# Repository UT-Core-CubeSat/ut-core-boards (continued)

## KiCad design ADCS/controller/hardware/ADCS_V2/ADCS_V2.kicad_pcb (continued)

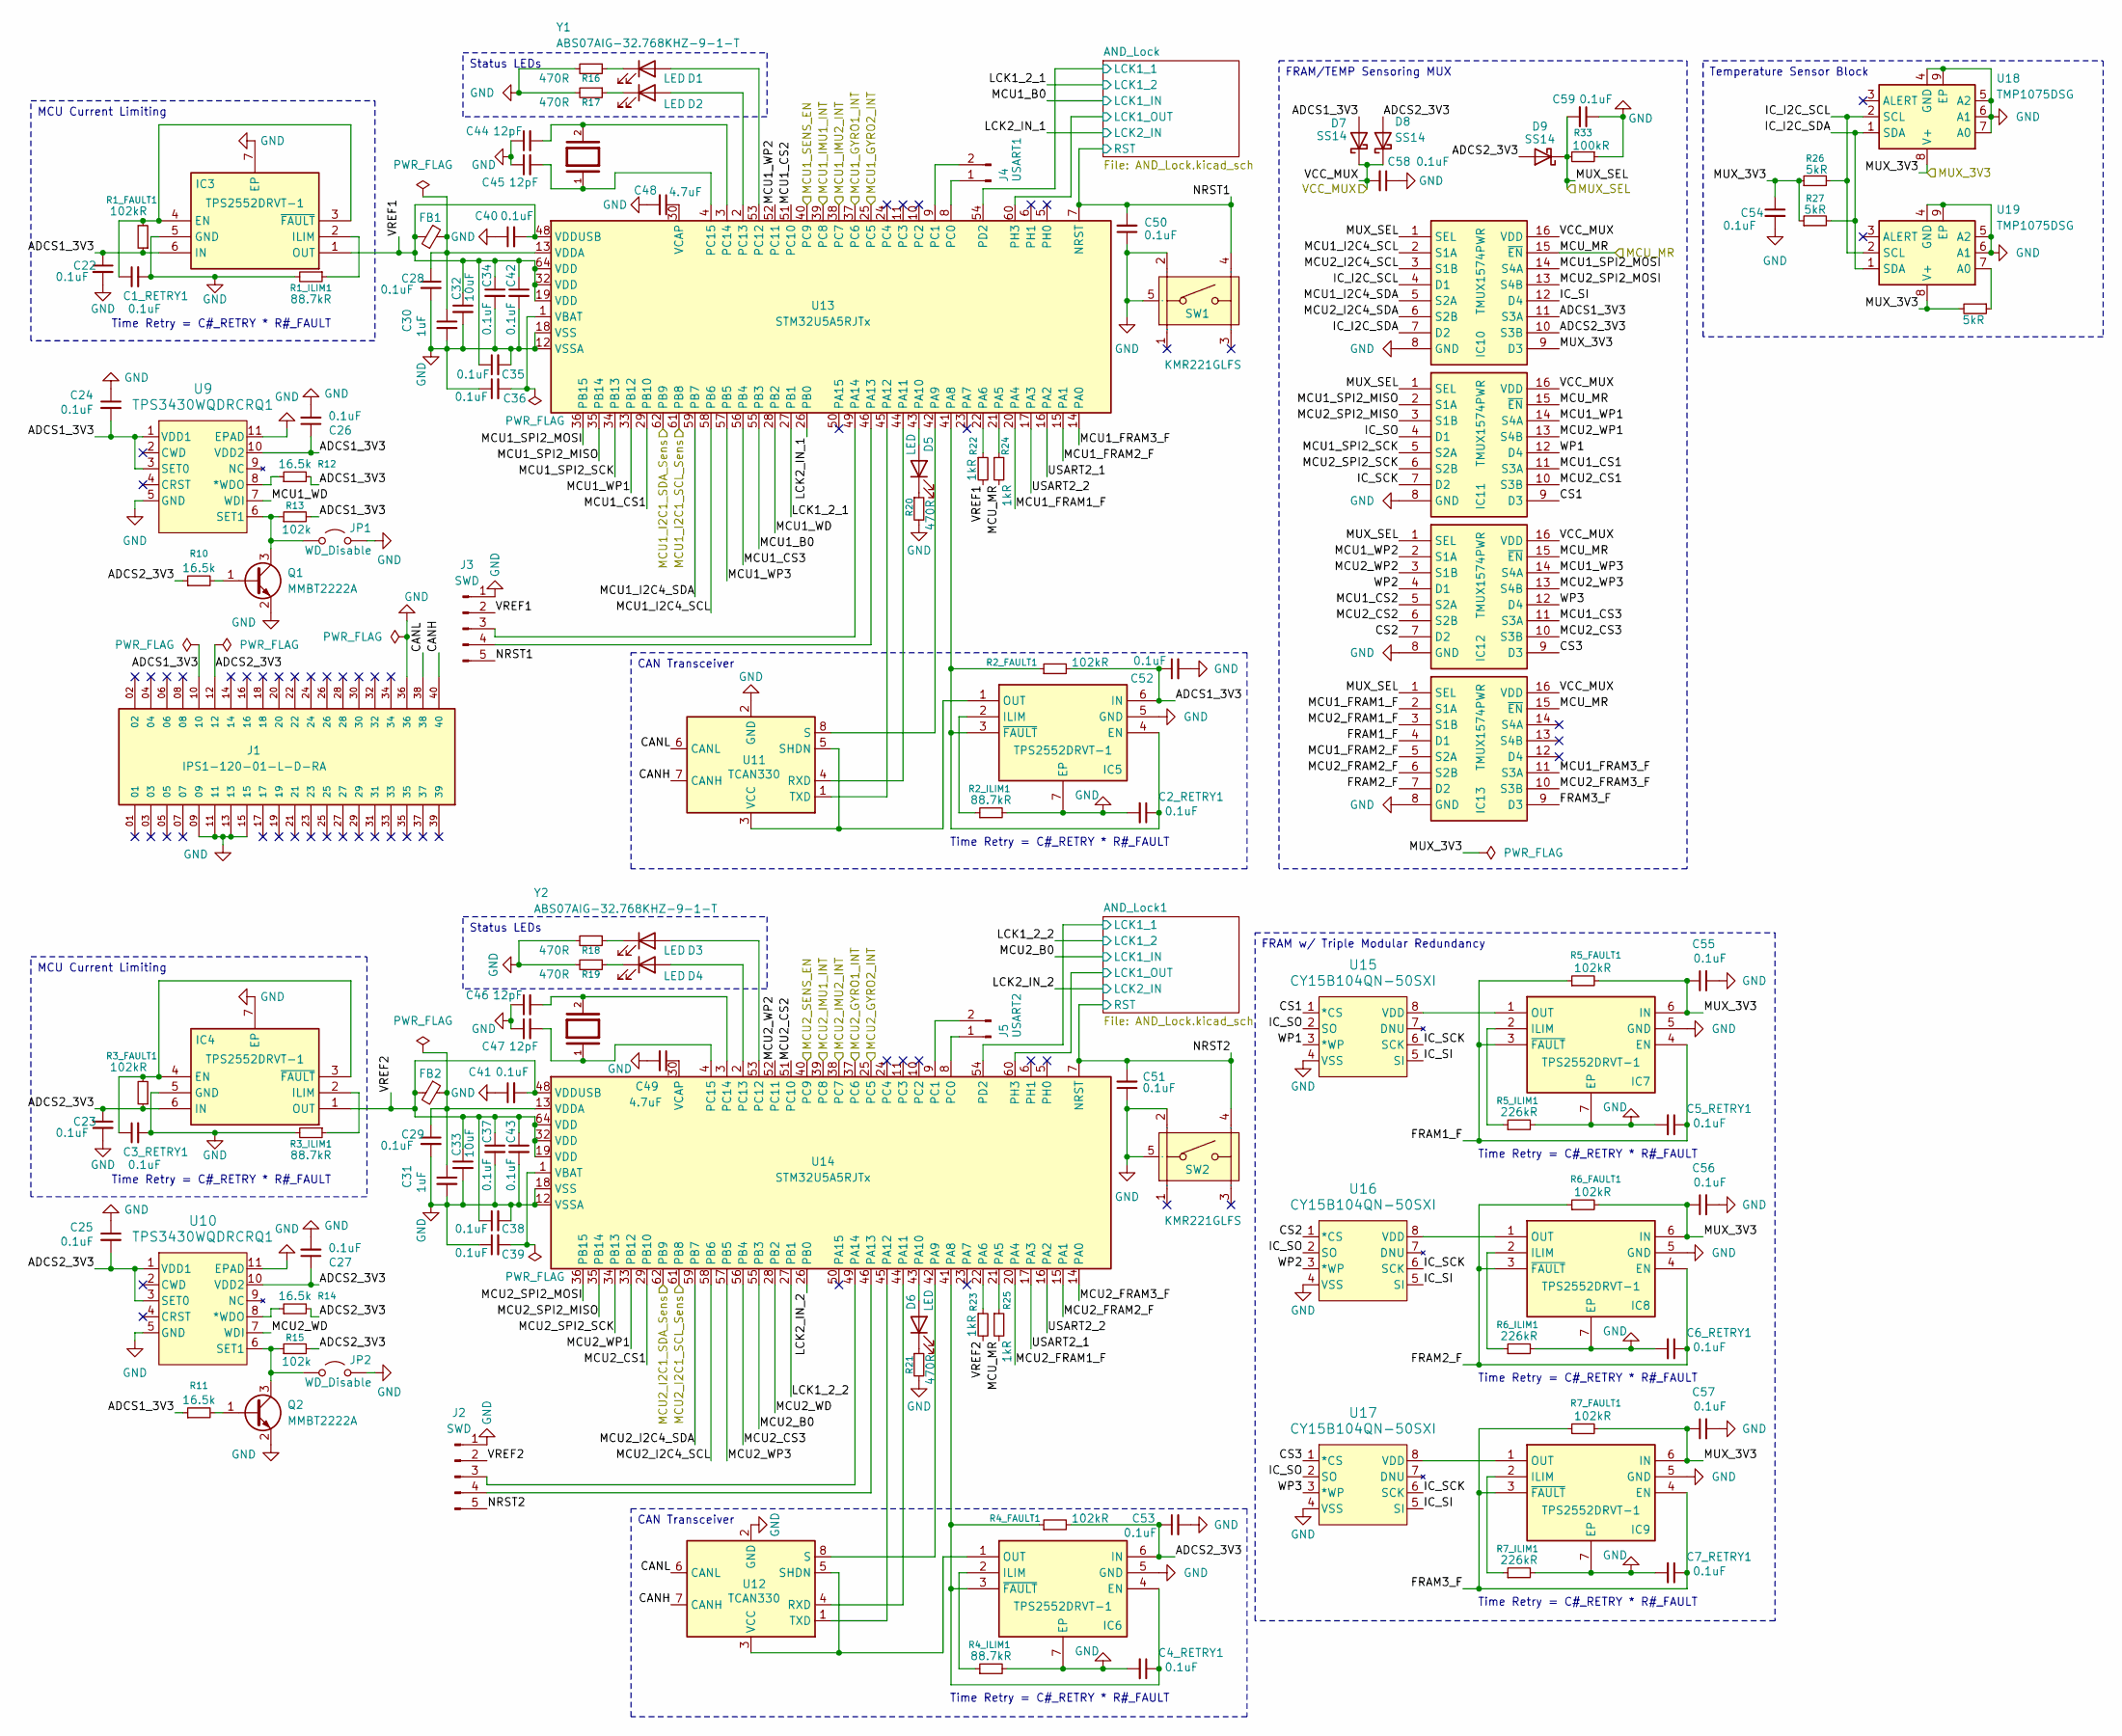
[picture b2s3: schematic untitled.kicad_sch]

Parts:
C1_RETRY1, C2_RETRY1, C3_RETRY1, C4_RETRY1, C5_RETRY1, C6_RETRY1, C7_RETRY1, C22, C23, C24, C25, C26, C27, C28, C29, C34, C35, C36, C37, C38, C39, C40, C41, C42, C43, C50, C51, C52, C53, C54, C55, C56, C57, C58, C59: 0.1uF; C_0603_1608Metric_Pad1.08x0.95mm_HandSolder
C30, C31: 1uF; C_0805_2012Metric_Pad1.18x1.45mm_HandSolder
C32, C33: 10uF; C_0805_2012Metric_Pad1.18x1.45mm_HandSolder
C44, C45, C46, C47: 12pF; C_0603_1608Metric_Pad1.08x0.95mm_HandSolder
C48, C49: 4.7uF; C_0805_2012Metric_Pad1.18x1.45mm_HandSolder
D1, D2, D3, D4, D5, D6: LED; LED_0201_0603Metric_Pad0.64x0.40mm_HandSolder
D7, D8, D9: SS14; D_SMA
FB1, FB2: FerriteBead_Small; R_0805_2012Metric_Pad1.20x1.40mm_HandSolder
IC3, IC4, IC5, IC6, IC7, IC8, IC9: TPS2552DRVT-1; Mouser Part Number 595-TPS2552DRVT-1
IC10, IC11, IC12, IC13: TMUX1574PWR; Mouser Part Number 595-TMUX1574PWR
J1: IPS1-120-01-L-D-RA
J2, J3: SWD; PinHeader_1x05_P2.54mm_Vertical
J4: USART1; PinHeader_1x02_P2.54mm_Vertical
J5: USART2; PinHeader_1x02_P2.54mm_Vertical
JP1, JP2: WD_Disable; TestPoint_2Pads_Pitch2.54mm_Drill0.8mm
Q1, Q2: MMBT2222A; SOT-23
R1_FAULT1, R2_FAULT1, R3_FAULT1, R4_FAULT1, R5_FAULT1, R6_FAULT1, R7_FAULT1: 102kR; R_0805_2012Metric_Pad1.20x1.40mm_HandSolder
R1_ILIM1, R2_ILIM1, R3_ILIM1, R4_ILIM1: 88.7kR; R_0805_2012Metric_Pad1.20x1.40mm_HandSolder
R5_ILIM1, R6_ILIM1, R7_ILIM1: 226kR; R_0805_2012Metric_Pad1.20x1.40mm_HandSolder
R10, R11, R12, R14: 16.5k; R_0805_2012Metric_Pad1.20x1.40mm_HandSolder
R13, R15: 102k; R_0805_2012Metric_Pad1.20x1.40mm_HandSolder
R16, R17, R18, R19, R20, R21: 470R; R_0805_2012Metric_Pad1.20x1.40mm_HandSolder
R22, R23, R24, R25: 1kR; R_0805_2012Metric_Pad1.20x1.40mm_HandSolder
R26, R27, R28: 5kR; R_0603_1608Metric_Pad0.98x0.95mm_HandSolder
R33: 100kR; R_0805_2012Metric_Pad1.20x1.40mm_HandSolder
SW1, SW2: KMR221GLFS; SW_KMR221GLFS; Manufacturer Part KMR221GLFS; LCSC Part Name 4.6*2.8*1.9mm 立贴 轻触开关
U9, U10: TPS3430WQDRCRQ1; SON50P300X300X100-11N
U11, U12: TCAN330; SOIC-8_3.9x4.9mm_P1.27mm
U13, U14: STM32U5A5RJTx; LQFP-64_10x10mm_P0.5mm
U15, U16, U17: CY15B104QN-50SXI
U18, U19: TMP1075DSG; WSON-8-1EP_2x2mm_P0.5mm_EP0.9x1.6mm
Y1, Y2: ABS07AIG-32.768KHZ-9-1-T; XTAL_ABS07AIG-32.768KHZ-9-1-T; PARTREV 6/7/2022

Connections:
/MUX/MCU_Block/ADCS1_3V3: C22.1, C24.2, C26.1, C52.1, D7.2 (A), IC3.6 (IN), IC5.6 (IN), IC10.11 (S3A), J1.10, R1_FAULT1.1, R2_FAULT1.2, R11.1, R12.2, R13.2, U9.1 (VDD1), U9.3 (SET0), U9.10 (VDD2)
/MUX/MCU_Block/ADCS2_3V3: C23.1, C25.2, C27.1, C53.1, D8.2 (A), D9.2 (A), IC4.6 (IN), IC6.6 (IN), IC10.10 (S3B), J1.12, R3_FAULT1.1, R4_FAULT1.2, R10.1, R14.2, R15.2, U10.1 (VDD1), U10.3 (SET0), U10.10 (VDD2)
/MUX/MCU_Block/AND_Lock1/LCK1_1: U14.54 (PD2); also elsewhere on the board
/MUX/MCU_Block/AND_Lock1/LCK1_OUT: U14.60 (PH3); also elsewhere on the board
/MUX/MCU_Block/AND_Lock/LCK1_1: U13.54 (PD2); also elsewhere on the board
/MUX/MCU_Block/AND_Lock/LCK1_OUT: U13.60 (PH3); also elsewhere on the board
/MUX/MCU_Block/CANH: J1.40, U11.7 (CANH), U12.7 (CANH)
/MUX/MCU_Block/CANL: J1.38, U11.6 (CANL), U12.6 (CANL)
/MUX/MCU_Block/CS1: IC11.9 (D3), U15.1 (*CS)
/MUX/MCU_Block/CS2: IC12.7 (D2), U16.1 (*CS)
/MUX/MCU_Block/CS3: IC12.9 (D3), U17.1 (*CS)
/MUX/MCU_Block/FRAM1_F: C5_RETRY1.1, IC7.3 (~FAULT), IC7.4 (EN), IC13.4 (D1), R5_FAULT1.1
/MUX/MCU_Block/FRAM2_F: C6_RETRY1.1, IC8.3 (~FAULT), IC8.4 (EN), IC13.7 (D2), R6_FAULT1.1
/MUX/MCU_Block/FRAM3_F: C7_RETRY1.1, IC9.3 (~FAULT), IC9.4 (EN), IC13.9 (D3), R7_FAULT1.1
/MUX/MCU_Block/IC_I2C_SCL: IC10.4 (D1), R26.2, U18.2 (SCL), U19.2 (SCL)
/MUX/MCU_Block/IC_I2C_SDA: IC10.7 (D2), R27.2, U18.1 (SDA), U19.1 (SDA)
/MUX/MCU_Block/IC_SCK: IC11.7 (D2), U15.6 (SCK), U16.6 (SCK), U17.6 (SCK)
/MUX/MCU_Block/IC_SI: IC10.12 (D4), U15.5 (SI), U16.5 (SI), U17.5 (SI)
/MUX/MCU_Block/IC_SO: IC11.4 (D1), U15.2 (SO), U16.2 (SO), U17.2 (SO)
/MUX/MCU_Block/LCK1_2_1: U13.27 (PB1); also elsewhere on the board
/MUX/MCU_Block/LCK1_2_2: U14.27 (PB1); also elsewhere on the board
/MUX/MCU_Block/LCK2_IN_1: U13.26 (PB0); also elsewhere on the board
/MUX/MCU_Block/LCK2_IN_2: U14.26 (PB0); also elsewhere on the board
/MUX/MCU_Block/MCU1_B0: U13.55 (PB3); also elsewhere on the board
/MUX/MCU_Block/MCU1_CS1: IC11.11 (S3A), U13.29 (PB10)
/MUX/MCU_Block/MCU1_CS2: IC12.5 (S2A), U13.51 (PC10)
/MUX/MCU_Block/MCU1_CS3: IC12.11 (S3A), U13.56 (PB4)
/MUX/MCU_Block/MCU1_FRAM1_F: IC13.2 (S1A), U13.20 (PA4)
/MUX/MCU_Block/MCU1_FRAM2_F: IC13.5 (S2A), U13.15 (PA1)
/MUX/MCU_Block/MCU1_FRAM3_F: IC13.11 (S3A), U13.14 (PA0)
/MUX/MCU_Block/MCU1_GYRO1_INT: U13.37 (PC6); also elsewhere on the board
/MUX/MCU_Block/MCU1_GYRO2_INT: U13.25 (PC5); also elsewhere on the board
/MUX/MCU_Block/MCU1_I2C1_SCL_Sens: U13.61 (PB8); also elsewhere on the board
/MUX/MCU_Block/MCU1_I2C1_SDA_Sens: U13.62 (PB9); also elsewhere on the board
/MUX/MCU_Block/MCU1_I2C4_SCL: IC10.2 (S1A), U13.58 (PB6)
/MUX/MCU_Block/MCU1_I2C4_SDA: IC10.5 (S2A), U13.59 (PB7)
/MUX/MCU_Block/MCU1_IMU1_INT: U13.39 (PC8); also elsewhere on the board
/MUX/MCU_Block/MCU1_IMU2_INT: U13.38 (PC7); also elsewhere on the board
/MUX/MCU_Block/MCU1_SENS_EN: U13.40 (PC9); also elsewhere on the board
/MUX/MCU_Block/MCU1_SPI2_MISO: IC11.2 (S1A), U13.35 (PB14)
/MUX/MCU_Block/MCU1_SPI2_MOSI: IC10.14 (S4A), U13.36 (PB15)
/MUX/MCU_Block/MCU1_SPI2_SCK: IC11.5 (S2A), U13.34 (PB13)
/MUX/MCU_Block/MCU1_WD: U9.7 (WDI), U13.28 (PB2)
/MUX/MCU_Block/MCU1_WP1: IC11.14 (S4A), U13.33 (PB12)
/MUX/MCU_Block/MCU1_WP2: IC12.2 (S1A), U13.52 (PC11)
/MUX/MCU_Block/MCU1_WP3: IC12.14 (S4A), U13.57 (PB5)
/MUX/MCU_Block/MCU2_B0: U14.55 (PB3); also elsewhere on the board
/MUX/MCU_Block/MCU2_CS1: IC11.10 (S3B), U14.29 (PB10)
/MUX/MCU_Block/MCU2_CS2: IC12.6 (S2B), U14.51 (PC10)
/MUX/MCU_Block/MCU2_CS3: IC12.10 (S3B), U14.56 (PB4)
/MUX/MCU_Block/MCU2_FRAM1_F: IC13.3 (S1B), U14.20 (PA4)
/MUX/MCU_Block/MCU2_FRAM2_F: IC13.6 (S2B), U14.15 (PA1)
/MUX/MCU_Block/MCU2_FRAM3_F: IC13.10 (S3B), U14.14 (PA0)
/MUX/MCU_Block/MCU2_GYRO1_INT: U14.37 (PC6); also elsewhere on the board
/MUX/MCU_Block/MCU2_GYRO2_INT: U14.25 (PC5); also elsewhere on the board
/MUX/MCU_Block/MCU2_I2C1_SCL_Sens: U14.61 (PB8); also elsewhere on the board
/MUX/MCU_Block/MCU2_I2C1_SDA_Sens: U14.62 (PB9); also elsewhere on the board
/MUX/MCU_Block/MCU2_I2C4_SCL: IC10.3 (S1B), U14.58 (PB6)
/MUX/MCU_Block/MCU2_I2C4_SDA: IC10.6 (S2B), U14.59 (PB7)
/MUX/MCU_Block/MCU2_IMU1_INT: U14.39 (PC8); also elsewhere on the board
/MUX/MCU_Block/MCU2_IMU2_INT: U14.38 (PC7); also elsewhere on the board
/MUX/MCU_Block/MCU2_SENS_EN: U14.40 (PC9); also elsewhere on the board
/MUX/MCU_Block/MCU2_SPI2_MISO: IC11.3 (S1B), U14.35 (PB14)
/MUX/MCU_Block/MCU2_SPI2_MOSI: IC10.13 (S4B), U14.36 (PB15)
/MUX/MCU_Block/MCU2_SPI2_SCK: IC11.6 (S2B), U14.34 (PB13)
/MUX/MCU_Block/MCU2_WD: U10.7 (WDI), U14.28 (PB2)
/MUX/MCU_Block/MCU2_WP1: IC11.13 (S4B), U14.33 (PB12)
/MUX/MCU_Block/MCU2_WP2: IC12.3 (S1B), U14.52 (PC11)
/MUX/MCU_Block/MCU2_WP3: IC12.13 (S4B), U14.57 (PB5)
/MUX/MCU_Block/NRST1: C50.2, J3.5, SW1.4, U13.7 (NRST); also elsewhere on the board
/MUX/MCU_Block/NRST2: C51.2, J2.5, SW2.4, U14.7 (NRST); also elsewhere on the board
/MUX/MCU_Block/USART2_1: U13.16 (PA2), U14.17 (PA3)
/MUX/MCU_Block/USART2_2: U13.17 (PA3), U14.16 (PA2)
/MUX/MCU_Block/VREF1: C32.1, C34.1, C35.1, C40.2, C42.1, FB1.2, IC3.1 (OUT), J3.2, R22.2, U13.19 (VDD), U13.32 (VDD), U13.48 (VDDUSB), U13.64 (VDD)
/MUX/MCU_Block/VREF2: C33.1, C37.1, C38.1, C41.2, C43.1, FB2.2, IC4.1 (OUT), J2.2, R23.2, U14.19 (VDD), U14.32 (VDD), U14.48 (VDDUSB), U14.64 (VDD)
/MUX/MCU_Block/WP1: IC11.12 (D4), U15.3 (*WP)
/MUX/MCU_Block/WP2: IC12.4 (D1), U16.3 (*WP)
/MUX/MCU_Block/WP3: IC12.12 (D4), U17.3 (*WP)
/MUX/MUX_MR: IC10.15 (~EN), IC11.15 (~EN), IC12.15 (~EN), IC13.15 (~EN), R24.2, R25.2; also elsewhere on the board
/MUX/MUX_SEL: C59.2, D9.1 (K), IC10.1 (SEL), IC11.1 (SEL), IC12.1 (SEL), IC13.1 (SEL), R33.2; also elsewhere on the board
/MUX/VCC_MUX: C58.2, D7.1 (K), D8.1 (K), IC10.16 (VDD), IC11.16 (VDD), IC12.16 (VDD), IC13.16 (VDD); also elsewhere on the board
/MUX_3V3: C54.1, C55.1, C56.1, C57.1, IC7.6 (IN), IC8.6 (IN), IC9.6 (IN), IC10.9 (D3), R5_FAULT1.2, R6_FAULT1.2, R7_FAULT1.2, R26.1, R27.1, R28.2, U18.8 (V+), U19.8 (V+); also elsewhere on the board
GND: C1_RETRY1.2, C2_RETRY1.2, C3_RETRY1.2, C4_RETRY1.2, C5_RETRY1.2, C6_RETRY1.2, C7_RETRY1.2, C22.2, C23.2, C24.1, C25.1, C26.2, C27.2, C28.2, C29.2, C30.2, C31.2, C32.2, C33.2, C34.2, C35.2, C36.1, C37.2, C38.2, C39.1, C40.1, C41.1, C42.2, C43.2, C44.1, C45.1, C46.1, C47.1, C48.2, C49.2, C50.1, C51.1, C52.2, C53.2, C54.2, C55.2, C56.2, C57.2, C58.1, C59.1, IC3.5 (GND), IC3.7 (EP), IC4.5 (GND), IC4.7 (EP), IC5.5 (GND), IC5.7 (EP), IC6.5 (GND), IC6.7 (EP), IC7.5 (GND), IC7.7 (EP), IC8.5 (GND), IC8.7 (EP), IC9.5 (GND), IC9.7 (EP), IC10.8 (GND), IC11.8 (GND), IC12.8 (GND), IC13.8 (GND), J1.09, J1.11, J1.13, J1.15, J1.36, J2.1, J3.1, JP1.2 (B), JP2.2 (B), Q1.2 (E), Q2.2 (E), R1_ILIM1.2, R2_ILIM1.2, R3_ILIM1.2, R4_ILIM1.2, R5_ILIM1.2, R6_ILIM1.2, R7_ILIM1.2, R16.2, R17.2, R18.2, R19.2, R20.2, R21.2, R33.1, SW1.2, SW1.5, SW2.2, SW2.5, U9.5 (GND), U9.11 (EPAD), U10.5 (GND), U10.11 (EPAD), U11.2 (GND), U12.2 (GND), U13.12 (VSSA), U13.18 (VSS), U13.31 (VSS), U13.47 (VSS), U13.63 (VSS), U14.12 (VSSA), U14.18 (VSS), U14.31 (VSS), U14.47 (VSS), U14.63 (VSS), U15.4 (VSS), U16.4 (VSS), U17.4 (VSS), U18.4 (GND), U18.5 (A2), U18.6 (A1), U18.7 (A0), U18.9 (EP), U19.4 (GND), U19.5 (A2), U19.6 (A1), U19.9 (EP); also elsewhere on the board
unnamed: D1.2 (A), U13.53 (PC12)
unnamed: D1.1 (K), R16.1
unnamed: D2.2 (A), U13.2 (PC13)
unnamed: D2.1 (K), R17.1
unnamed: D3.2 (A), U14.53 (PC12)
unnamed: D3.1 (K), R18.1
unnamed: D4.2 (A), U14.2 (PC13)
unnamed: D4.1 (K), R19.1
unnamed: D5.2 (A), U13.43 (PA10)
unnamed: D5.1 (K), R20.1
unnamed: D6.2 (A), U14.43 (PA10)
unnamed: D6.1 (K), R21.1
unnamed: C1_RETRY1.1, IC3.3 (~FAULT), IC3.4 (EN), R1_FAULT1.2
unnamed: IC3.2 (ILIM), R1_ILIM1.1
unnamed: C3_RETRY1.1, IC4.3 (~FAULT), IC4.4 (EN), R3_FAULT1.2
unnamed: IC4.2 (ILIM), R3_ILIM1.1
unnamed: C2_RETRY1.1, IC5.3 (~FAULT), IC5.4 (EN), R2_FAULT1.1, U13.41 (PA8)
unnamed: IC5.2 (ILIM), R2_ILIM1.1
unnamed: IC5.1 (OUT), U11.3 (VCC), U11.5 (SHDN)
unnamed: C4_RETRY1.1, IC6.3 (~FAULT), IC6.4 (EN), R4_FAULT1.1, U14.41 (PA8)
unnamed: IC6.2 (ILIM), R4_ILIM1.1
unnamed: IC6.1 (OUT), U12.3 (VCC), U12.5 (SHDN)
unnamed: IC7.2 (ILIM), R5_ILIM1.1
unnamed: IC7.1 (OUT), U15.8 (VDD)
unnamed: IC8.2 (ILIM), R6_ILIM1.1
unnamed: IC8.1 (OUT), U16.8 (VDD)
unnamed: IC9.2 (ILIM), R7_ILIM1.1
unnamed: IC9.1 (OUT), U17.8 (VDD)
unnamed: J2.3, U14.49 (PA14)
unnamed: J2.4, U14.46 (PA13)
unnamed: J3.3, U13.49 (PA14)
unnamed: J3.4, U13.46 (PA13)
unnamed: J4.1, U13.8 (PC0)
unnamed: J4.2, U13.9 (PC1)
unnamed: J5.1, U14.8 (PC0)
unnamed: J5.2, U14.9 (PC1)
unnamed: JP1.1 (A), Q1.3 (C), R13.1, U9.6 (SET1)
unnamed: JP2.1 (A), Q2.3 (C), R15.1, U10.6 (SET1)
unnamed: Q1.1 (B), R10.2
unnamed: Q2.1 (B), R11.2
unnamed: R12.1, U9.8 (*WDO)
unnamed: R14.1, U10.8 (*WDO)
unnamed: U11.4 (RXD), U13.44 (PA11)
unnamed: U11.8 (S), U13.42 (PA9)
unnamed: U11.1 (TXD), U13.45 (PA12)
unnamed: U12.4 (RXD), U14.44 (PA11)
unnamed: U12.8 (S), U14.42 (PA9)
unnamed: U12.1 (TXD), U14.45 (PA12)
unnamed: R24.1, U13.21 (PA5)
unnamed: R22.1, U13.22 (PA6)
unnamed: C44.2, U13.3 (PC14), Y1.2
unnamed: C45.2, U13.4 (PC15), Y1.1
unnamed: C36.2, U13.1 (VBAT)
unnamed: C48.1, U13.30 (VCAP)
unnamed: C28.1, C30.1, FB1.1, U13.13 (VDDA)
unnamed: R25.1, U14.21 (PA5)
unnamed: R23.1, U14.22 (PA6)
unnamed: C46.2, U14.3 (PC14), Y2.2
unnamed: C47.2, U14.4 (PC15), Y2.1
unnamed: C39.2, U14.1 (VBAT)
unnamed: C49.1, U14.30 (VCAP)
unnamed: C29.1, C31.1, FB2.1, U14.13 (VDDA)
unnamed: R28.1, U19.7 (A0)

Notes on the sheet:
Time Retry = C#_RETRY * R#_FAULT
Status LEDs
MCU Current Limiting
FRAM/TEMP Sensoring MUX
CAN Transceiver
FRAM w/ Triple Modular Redundancy
Temperature Sensor Block

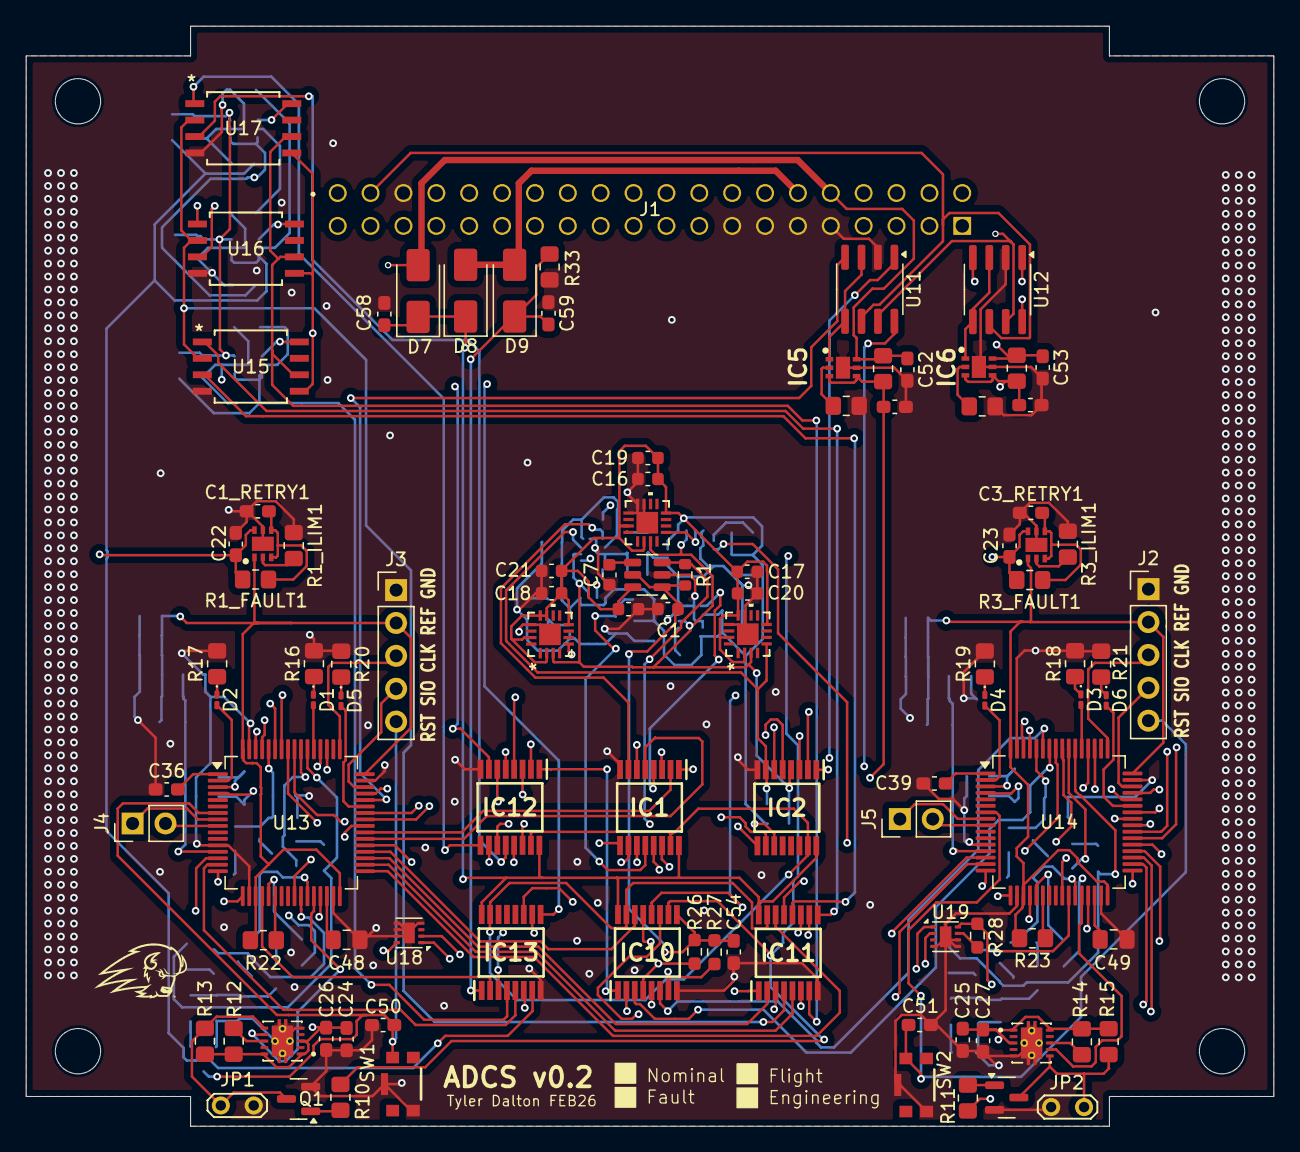
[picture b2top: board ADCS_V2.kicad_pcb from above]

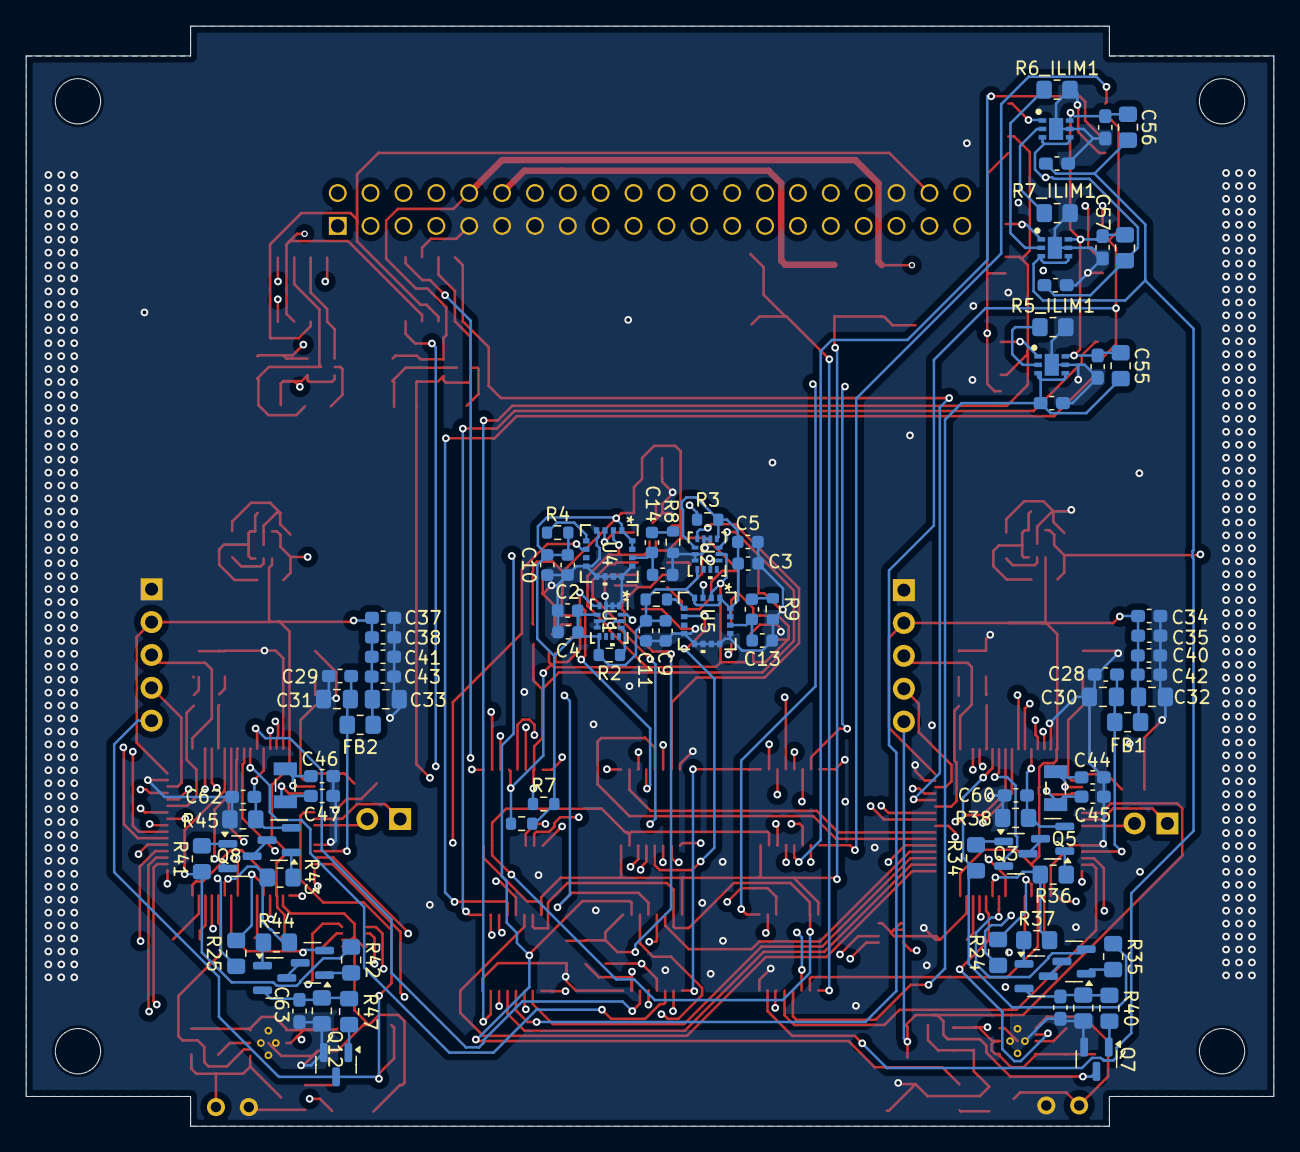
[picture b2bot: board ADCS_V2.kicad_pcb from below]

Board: 4 copper layers, 96.4 x 85.0 mm, 193 parts (91 on the bottom side), 179 nets.

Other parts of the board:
C60, C61, C62, C63: 0.1uF; C_0603_1608Metric_Pad1.08x0.95mm_HandSolder
Q3, Q4, Q8, Q9: MMBTA94; SOT-23
Q5, Q6, Q7, Q10, Q11, Q12: MMBT2222A; SOT-23
R34, R35, R36, R37, R41, R42, R43, R44: 10kR; R_0805_2012Metric_Pad1.20x1.40mm_HandSolder
R38, R39, R45, R46: 5kR; R_0805_2012Metric_Pad1.20x1.40mm_HandSolder
R40, R47: 100kR; R_0805_2012Metric_Pad1.20x1.40mm_HandSolder

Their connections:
/MUX/MCU_Block/AND_Lock1/LCK1_1: R41.1, R42.1; also elsewhere on the board
/MUX/MCU_Block/AND_Lock1/LCK1_OUT: C62.1, Q10.2 (E), R45.1; also elsewhere on the board
/MUX/MCU_Block/AND_Lock/LCK1_1: R34.1, R35.1; also elsewhere on the board
/MUX/MCU_Block/AND_Lock/LCK1_OUT: C60.1, Q5.2 (E), R38.1; also elsewhere on the board
/MUX/MCU_Block/LCK1_2_1: R36.2, R37.2; also elsewhere on the board
/MUX/MCU_Block/LCK1_2_2: R43.2, R44.2; also elsewhere on the board
/MUX/MCU_Block/LCK2_IN_1: Q4.2 (E); also elsewhere on the board
/MUX/MCU_Block/LCK2_IN_2: Q9.2 (E); also elsewhere on the board
/MUX/MCU_Block/MCU1_B0: Q3.2 (E); also elsewhere on the board
/MUX/MCU_Block/MCU2_B0: Q8.2 (E); also elsewhere on the board
/MUX/MCU_Block/NRST1: Q7.3 (C); also elsewhere on the board
/MUX/MCU_Block/NRST2: Q12.3 (C); also elsewhere on the board
GND: C60.2, C61.2, C62.2, C63.2, Q7.2 (E), Q12.2 (E), R38.2, R39.2, R45.2, R46.2; also elsewhere on the board
unnamed: Q3.1 (B), R34.2
unnamed: Q3.3 (C), Q5.3 (C)
unnamed: Q4.1 (B), R35.2
unnamed: Q4.3 (C), Q6.3 (C)
unnamed: Q5.1 (B), R36.1
unnamed: Q6.1 (B), R37.1
unnamed: C61.1, Q6.2 (E), R39.1, R40.1
unnamed: Q7.1 (B), R40.2
unnamed: Q8.1 (B), R41.2
unnamed: Q9.1 (B), R42.2
unnamed: Q10.1 (B), R43.1
unnamed: Q8.3 (C), Q10.3 (C)
unnamed: Q11.1 (B), R44.1
unnamed: Q9.3 (C), Q11.3 (C)
unnamed: C63.1, Q11.2 (E), R46.1, R47.1
unnamed: Q12.1 (B), R47.2
